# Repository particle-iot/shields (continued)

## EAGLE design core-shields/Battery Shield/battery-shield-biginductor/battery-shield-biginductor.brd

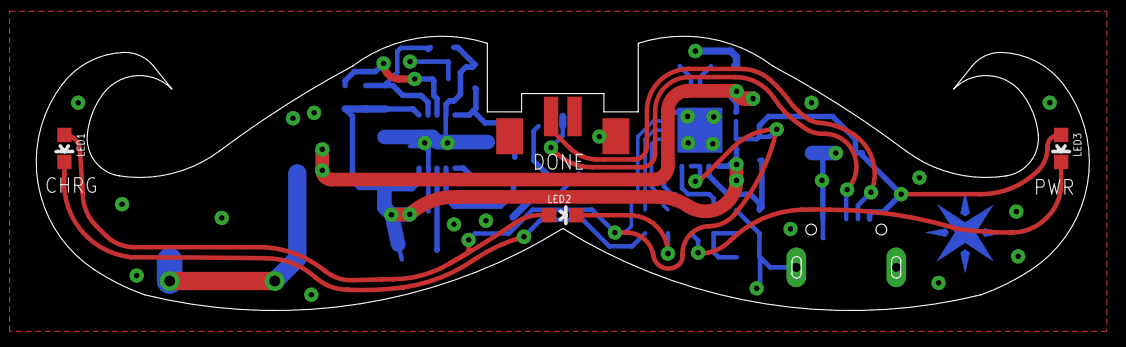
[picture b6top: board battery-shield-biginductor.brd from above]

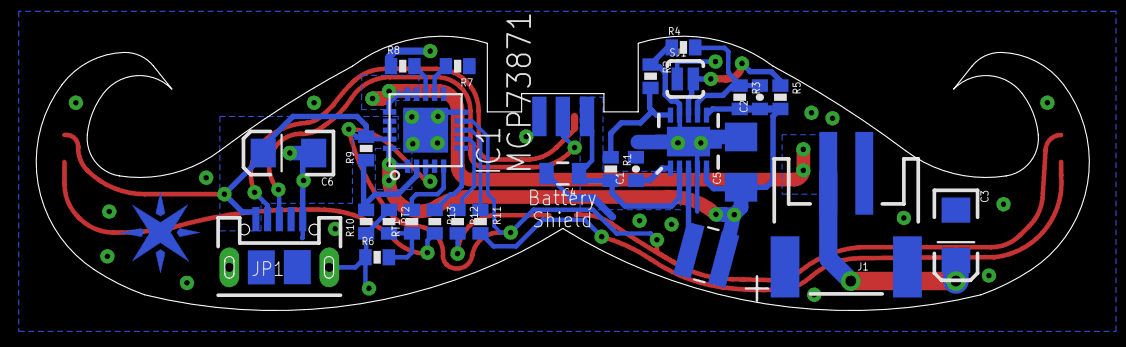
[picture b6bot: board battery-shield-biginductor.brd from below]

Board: 2 copper layers, 58.5 x 15.2 mm, 32 parts (28 on the bottom side), 24 nets.

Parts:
C1, C2: 0.1uF; 0402-CAP
C3, C6: 10uF; EIA3216
C4: 22uF; 0805
C5: 10uF; 1206
IC1: MCP73871; QFN20
J1: JST-2-SMD
JP1: USBUSB-MICROB-SLOT-HOLE; USB-MICROB-SLOT-HOLE
JP2: USBFCI; USB-MICROB-MALE-SANDWICH
L1: 4.7uH, 1.2A; INDUCTOR-VLS-E
LED1: Yellow; LED-0603
LED2: Green; LED-0603
LED3: Red; LED-0603
R1, R3: 2M; 0402-RES
R2, R4: 220K; 0402-RES
R5, R6: 10K; 0402-RES
R7: 100k; 0402-RES
R8: 2K; 0402-RES
R9: 270K; 0402-RES
R10: 100K; 0402-RES
R11, R12, R13: 1K; 0402-RES
RT1: 1K; 0402-RES
RT2: 150K; 0402-RES
SJ1: SOLDERJUMPERNO; SJ_2S-NO
U1: TPS61200; QFN-10_PAD
U$2: SPARK_LOGO_PLUS_PLANE

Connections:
+5V: C4.1, JP2.VBUS, R1.2, U1.2
D+: JP1.D+, JP2.D+
D-: JP1.D-, JP2.D-
DGND: R2.1, R4.1, U1.9
GND: C1.2, C3.C, C4.2, C5.2, C6.C, IC1.10, IC1.11, J1.1, JP1.GND, JP1.MT1, JP1.MT2, JP2.GND, JP2.GNDPAD1, JP2.GNDPAD2, R6.1, R7.1, R8.1, R10.1, RT2.1, SJ1.1, U1.4, U1.11, U1.12, U1.13, U1.14, U1.15
unnamed: L1.P$2, U1.3
unnamed: C1.1, U1.1
unnamed: C2.2, R3.1, R4.2, U1.7
unnamed: R1.1, R2.2, U1.10
unnamed: C3.A, IC1.14, IC1.15, IC1.16, J1.2
unnamed: IC1.8, R11.1
unnamed: R6.2, RT1.1, RT2.2
unnamed: LED1.C, R11.2
unnamed: IC1.5, RT1.2
unnamed: LED2.C, R12.2
unnamed: IC1.12, R7.2
unnamed: IC1.2, R9.1, R10.2
unnamed: IC1.13, R8.2
unnamed: IC1.7, R12.1
unnamed: IC1.6, R13.1
unnamed: LED3.C, R13.2
unnamed: R5.1, SJ1.2, U1.8
VBATT_OUT: C2.1, C5.1, IC1.1, IC1.20, L1.P$1, R3.2, R5.2, U1.5, U1.6
VBUS: C6.A, IC1.3, IC1.4, IC1.9, IC1.17, IC1.18, IC1.19, JP1.VBUS, LED1.A, LED2.A, LED3.A, R9.2

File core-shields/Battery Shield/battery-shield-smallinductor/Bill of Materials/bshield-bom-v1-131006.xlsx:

| PROJECT NAME |  | SPARK BATTERY SHIELD
 | LAST UPDATED |  | 41653
 | BSHIELD
 | Qty | AQS P/N | Device | Minimum Specification | Component Value (if different) | Package/Case | Designator | AVL | AVL P/N | Additional Comments
 | 1 | 307-20-301621 | Fab PCB | Double Sided, 1.0mm, 1OZ, Electroless Nickel Immersion Gold, Black Solder Mask,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 |  |  |  |  |  | CONSIGNED BY SPARK
 | 1 | HL-121-12-301353 | Ceramic Capacitor | 10uF, 10V, 10% |  | 1206 | C5 | Taiyo | LMK316BJ106KLHT
 | 2 | HL-121-02-301600 | Ceramic Capacitor | 0.1uF, 10V, 10% |  | 0402 | C1, C2 | RongFu | 0402B104K01A
 | 1 | HL-121-10-301613 | Ceramic Capacitor | 22uF, 10V, 10% |  | 0805 | C4 | Taiyo Yuden | LMK212BJ226MG-T
 | 1 | HL-221-90-301464 | DC to DC Booster | 1.2A |  | QFN10 Exposed Pad | U1 | Texas Instruments | TPS61200DRCT
 | 1 | 161-50-301205 | Inductor | 4.7uH, 25%, 1.0A |  | 3030 (3x3mm) | L1 | Sumida America | CDRH2D18/HPNP-4R7NC | CONSIGNED BY SPARK
 | 1 | HL-511-30-301381 | JST Right-Angle Connector | 2mm, 2-pin, Male, SMT |  | 2-Pin SMT, Right-Angle | J1 | Kaweei | CW2001-02T1-H01-B
 | 1 | HL-414-10-301291 | LED | Yellow |  | 0603 | LED1 | AQS supplier | WLUY0603A-25
 | 1 | HL-414-10-301292 | LED | Green |  | 0603 | LED2 | AQS supplier | WLG0603A-02-I
 | 1 | HL-414-10-301282 | LED | Blue |  | 0603 | LED3 | AQS supplier | WLUB0603A-341
 | 1 | HL-411-60-301004 | Li-Ion Rechargeable Battery | 3.7V, 400mAh, JST-PH-2P connector |  | JST-PH connector, 2-pin | BT1 | Pkcell | LP062530
 | 1 | 223-40-301231 | LiPo Charger | 4.4V-6.0V Input |  | QFN20 Exposed Pad (4x4) | IC1 | Microchip Technology | MCP73871T-2CCI/ML | CONSIGNED BY SPARK
 | 2 | HL-101-10-302444 | Resistor | 2M, 1%, 1/10W |  | 0402 | R1, R3 | Velox Vendor | SMD0402205F
 | 2 | HL-101-10-302445 | Resistor | 100K, 1%, 1/10W |  | 0402 | R7, R10 | Velox Vendor | SMD0402104F
 | 4 | HL-101-10-302446 | Resistor | 1K, 1%, 1/10W |  | 0402 | R11, R12, R13, RT1 | Velox Vendor | SMD0402102F
 | 2 | HL-101-10-302447 | Resistor | 220K, 1%, 1/10W |  | 0402 | R2, R4 | Velox Vendor | SMD0402223F
 | 1 | HL-101-10-302448 | Resistor | 2K, 1%, 1/10W |  | 0402 | R8 | Velox Vendor | SMD0402202F
 | 1 | HL-101-10-302449 | Resistor | 270K, 1%, 1/10W |  | 0402 | R9 | Velox Vendor | SMD0402273F
 | 1 | HL-101-10-302443 | Resistor | 150K, 1%, 1/10W |  | 0402 | RT2 | RongFu | 0402WAF0150KTCE
 | 2 | HL-101-10-302450 | Resistor | 10K, 1%, 1/10W |  | 0402 | R5, R6 | Panasonic Electronic Components | ERJ-2RKF1002X
 | 2 | HL-121-12-301350 | Tantalum Capacitor | 10uF, 16V, 10% |  | 1206 (3216) | C3, C6 | AVX | TAJA106K010RNJ.
 | 1 | HL-515-40-301729 | USB-Micro B Connector - Female | USB-Micro B, SMT with TH Board Guides |  | USB-MICROB | JP1 | Kaweei | CMCUSB-5BFM2G-01-D
 | 1 | 511-30-301385 | USB-Micro B Connector - Male | USB-Micro B, SMT with Sandwich Guides |  | USB-MICROB | JP2 | FCI | 10104109-0001LF | CONSIGNED BY SPARK
 | PACKAGING
 | Qty |  | Device | Minimum Specification | Component Value (if different) | Package/Case | Designator | AVL | AVL P/N | Additional Comments
 | 1 | HL-901-00-301327 | Small Static Bag |  |  | 130 x 100mm
 | 1 | HL-901-00-301332 | Small Static Bubble Bag |  |  | 110 x 140mm, red
 | 1 | 831-10-301388 | "STICK-BS" sticker | Shield Description and UPC Barcode |  | 8 x 10 cm |  |  |  | CONSIGNED BY SPARK
